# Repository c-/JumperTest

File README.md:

# JumperTest
quick and dirty test of doing sane 1-sided PCB's using a easy-to-add jumper symbol

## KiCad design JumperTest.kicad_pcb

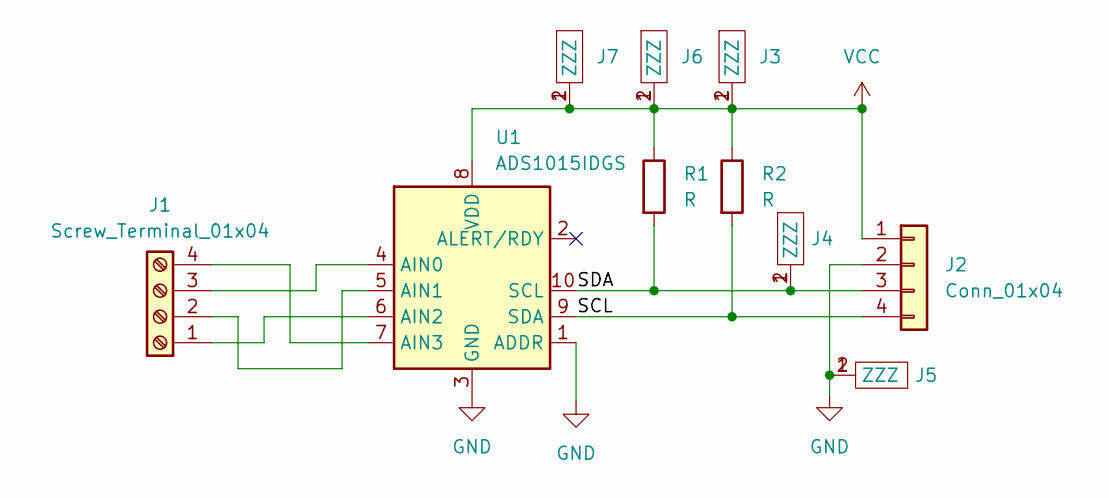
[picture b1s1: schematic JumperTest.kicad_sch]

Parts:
J1: Screw_Terminal_01x04; TerminalBlock_Phoenix_PT-1,5-4-3.5-H_1x04_P3.50mm_Horizontal
J2: Conn_01x04; PinHeader_1x04_P2.54mm_Horizontal
J3, J4, J5, J6, J7: R_0805_2012Metric_Pad1.20x1.40mm_HandSolder
R1, R2: R; R_0805_2012Metric_Pad1.20x1.40mm_HandSolder
U1: ADS1015IDGS; TSSOP-10_3x3mm_P0.5mm

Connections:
/SCL: J2.4, R2.2, U1.9 (SDA)
/SDA: J2.3, J4.1 (ZZZ), J4.2 (ZZZ), R1.2, U1.10 (SCL)
GND: J2.2, J5.1 (ZZZ), J5.2 (ZZZ), U1.1 (ADDR), U1.3 (GND)
unnamed: J1.1, U1.6 (AIN2)
unnamed: J1.2, U1.5 (AIN1)
unnamed: J1.3, U1.4 (AIN0)
unnamed: J1.4, U1.7 (AIN3)
VCC: J2.1, J3.1 (ZZZ), J3.2 (ZZZ), J6.1 (ZZZ), J6.2 (ZZZ), J7.1 (ZZZ), J7.2 (ZZZ), R1.1, R2.1, U1.8 (VDD)

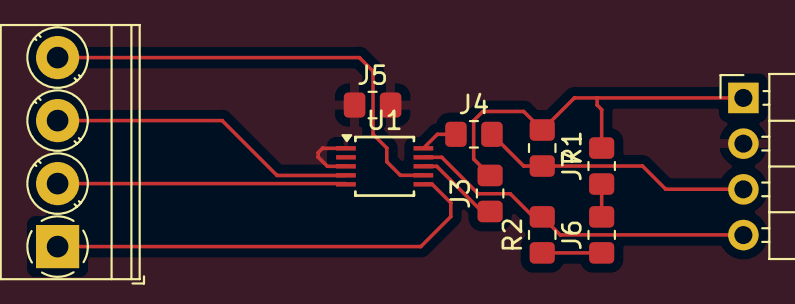
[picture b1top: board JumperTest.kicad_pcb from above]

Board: 2 copper layers, 10 parts (0 on the bottom side), 8 nets.
